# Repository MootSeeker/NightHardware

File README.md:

# NightHardware
PCB for Nightlight project

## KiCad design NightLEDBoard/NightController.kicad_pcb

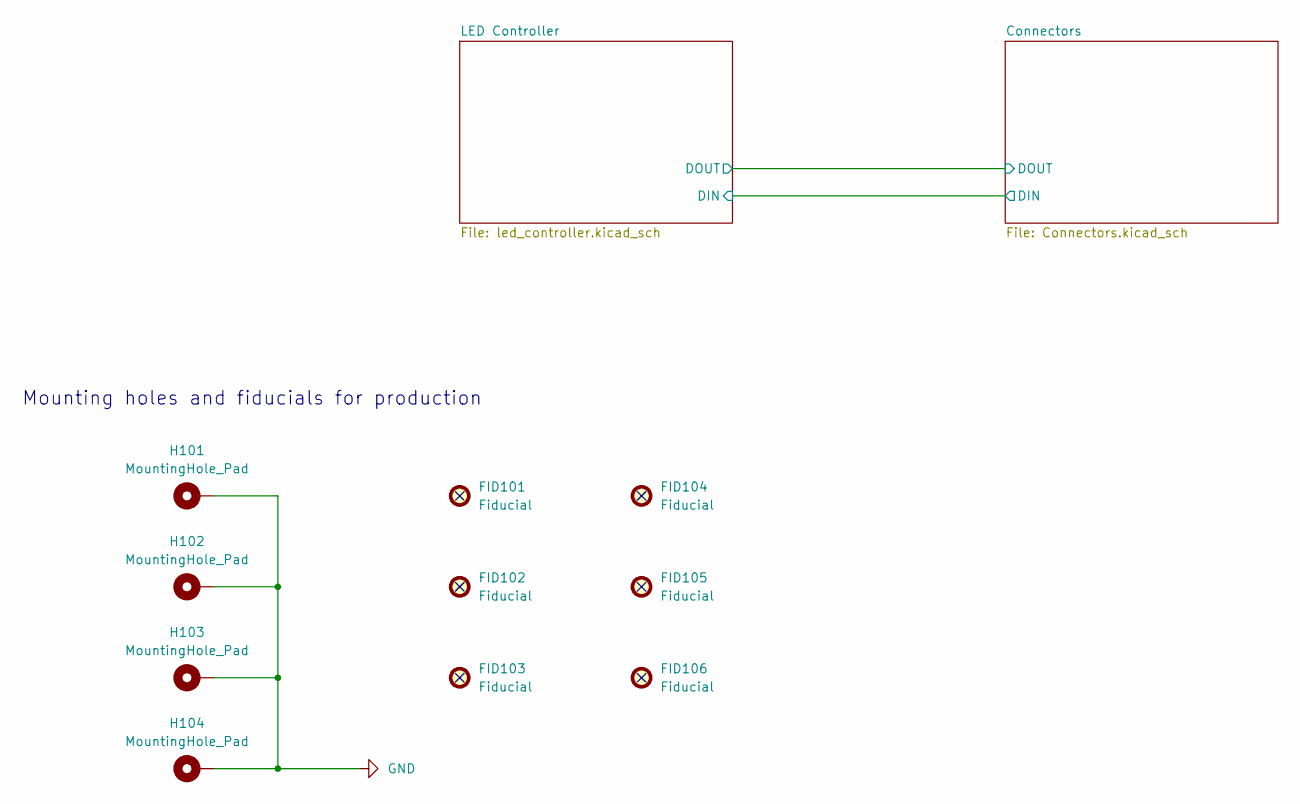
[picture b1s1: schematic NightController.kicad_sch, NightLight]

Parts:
FID101, FID102, FID103, FID104, FID105, FID106: Fiducial; Fiducial_0.5mm_Mask1mm
H101, H102, H103, H104: MountingHole_Pad; MountingHole_3.2mm_M3_Pad_Via

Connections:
GND: H101.1, H102.1, H103.1, H104.1; also elsewhere on the board

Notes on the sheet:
Mounting holes and fiducials for production

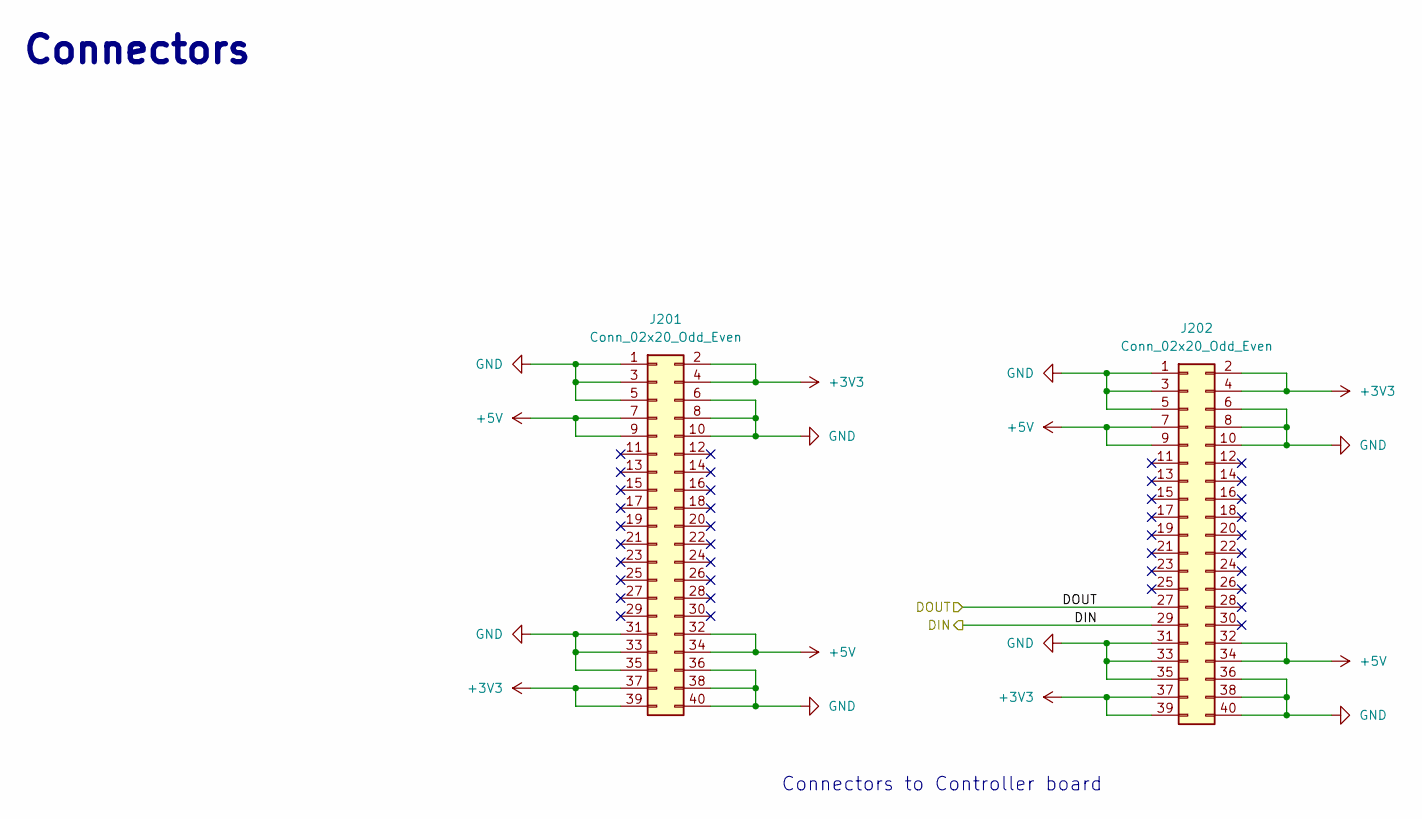
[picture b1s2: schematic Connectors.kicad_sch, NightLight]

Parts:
J201, J202: Conn_02x20_Odd_Even; Molex_SlimStack_54722-0404_2x20_P0.50mm_Vertical

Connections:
+3V3: J201.2, J201.4, J201.37, J201.39, J202.2, J202.4, J202.37, J202.39
+5V: J201.7, J201.9, J201.32, J201.34, J202.7, J202.9, J202.32, J202.34; also elsewhere on the board
/Connectors/DIN: J202.29; also elsewhere on the board
/Connectors/DOUT: J202.27; also elsewhere on the board
GND: J201.1, J201.3, J201.5, J201.6, J201.8, J201.10, J201.31, J201.33, J201.35, J201.36, J201.38, J201.40, J202.1, J202.3, J202.5, J202.6, J202.8, J202.10, J202.31, J202.33, J202.35, J202.36, J202.38, J202.40; also elsewhere on the board

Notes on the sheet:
Connectors to Controller board
Connectors

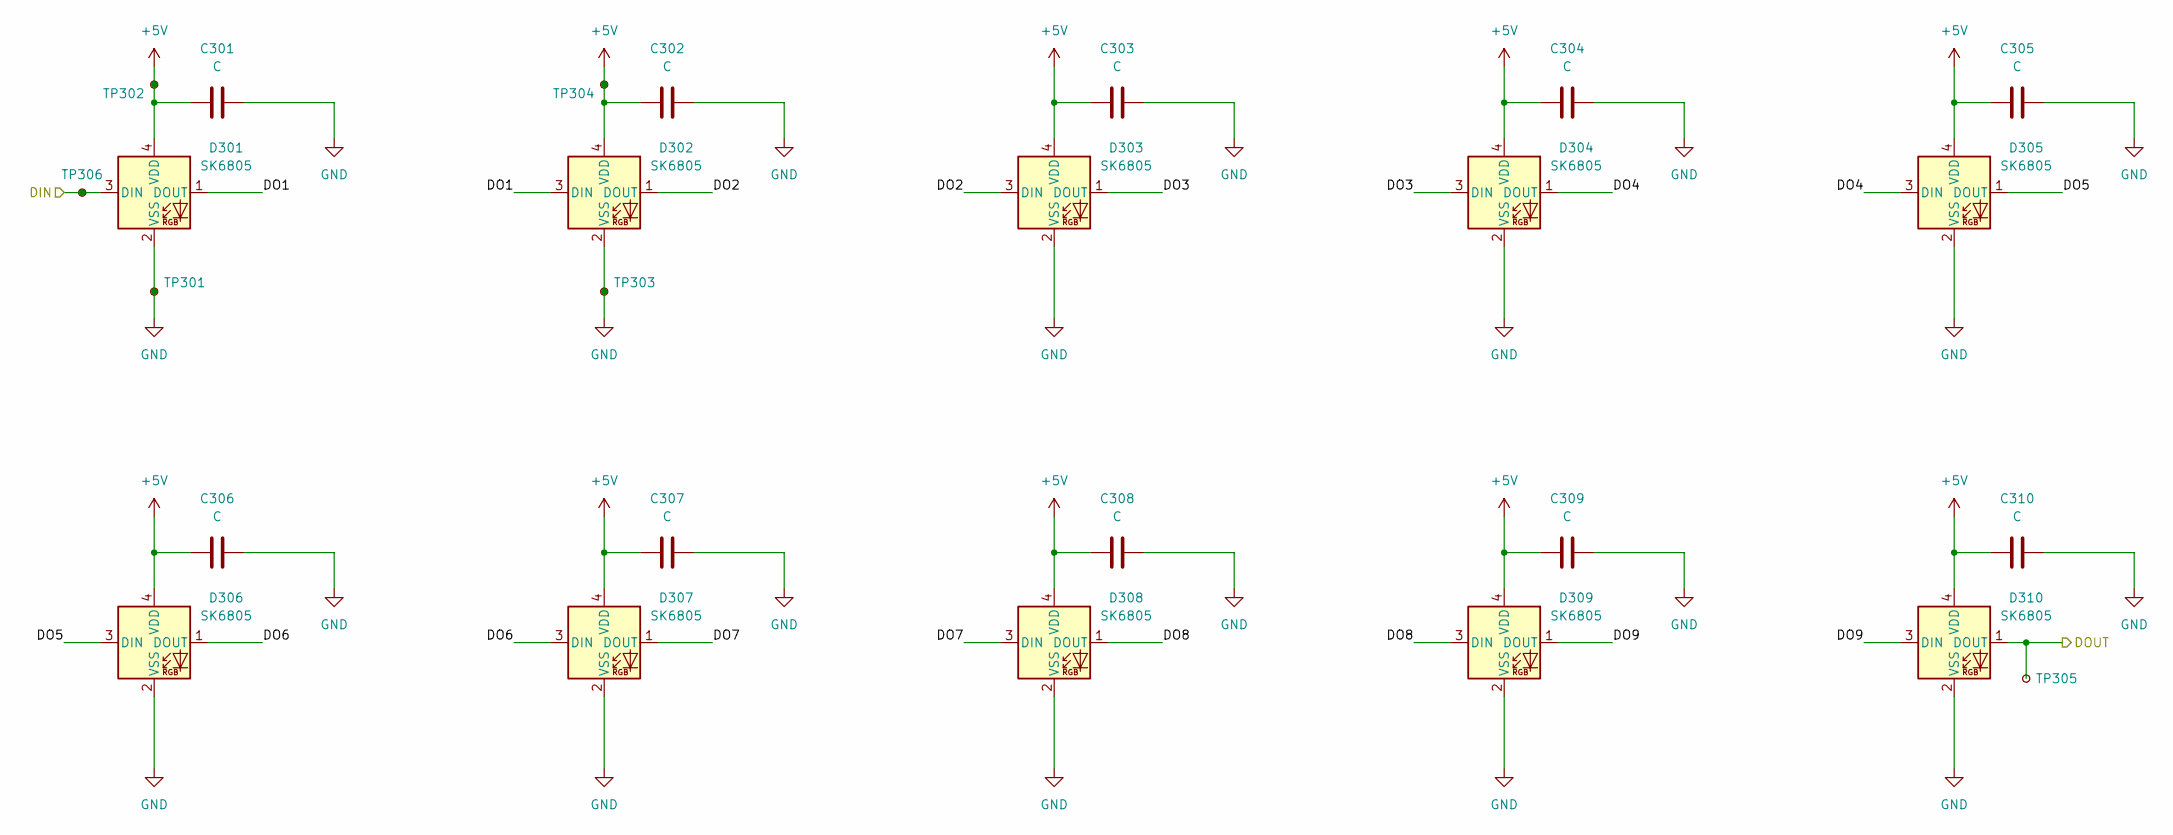
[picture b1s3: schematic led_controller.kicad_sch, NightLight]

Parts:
C301, C302, C303, C304, C305, C306, C307, C308, C309, C310: C; C_0402_1005Metric_Pad0.74x0.62mm_HandSolder
D301, D302, D303, D304, D305, D306, D307, D308, D309, D310: SK6805; LED_SK6805_PLCC4_2.4x2.7mm_P1.3mm
TP301, TP302, TP303, TP304, TP305, TP306: TestPoint_Small; TestPoint_Loop_D1.80mm_Drill1.0mm_Beaded

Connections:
+5V: C301.1, C302.1, C303.1, C304.1, C305.1, C306.1, C307.1, C308.1, C309.1, C310.1, D301.4 (VDD), D302.4 (VDD), D303.4 (VDD), D304.4 (VDD), D305.4 (VDD), D306.4 (VDD), D307.4 (VDD), D308.4 (VDD), D309.4 (VDD), D310.4 (VDD), TP302.1, TP304.1; also elsewhere on the board
/Connectors/DIN: D301.3 (DIN), TP306.1; also elsewhere on the board
/Connectors/DOUT: D310.1 (DOUT), TP305.1; also elsewhere on the board
/LED Controller/DO1: D301.1 (DOUT), D302.3 (DIN)
/LED Controller/DO2: D302.1 (DOUT), D303.3 (DIN)
/LED Controller/DO3: D303.1 (DOUT), D304.3 (DIN)
/LED Controller/DO4: D304.1 (DOUT), D305.3 (DIN)
/LED Controller/DO5: D305.1 (DOUT), D306.3 (DIN)
/LED Controller/DO6: D306.1 (DOUT), D307.3 (DIN)
/LED Controller/DO7: D307.1 (DOUT), D308.3 (DIN)
/LED Controller/DO8: D308.1 (DOUT), D309.3 (DIN)
/LED Controller/DO9: D309.1 (DOUT), D310.3 (DIN)
GND: C301.2, C302.2, C303.2, C304.2, C305.2, C306.2, C307.2, C308.2, C309.2, C310.2, D301.2 (VSS), D302.2 (VSS), D303.2 (VSS), D304.2 (VSS), D305.2 (VSS), D306.2 (VSS), D307.2 (VSS), D308.2 (VSS), D309.2 (VSS), D310.2 (VSS), TP301.1, TP303.1; also elsewhere on the board

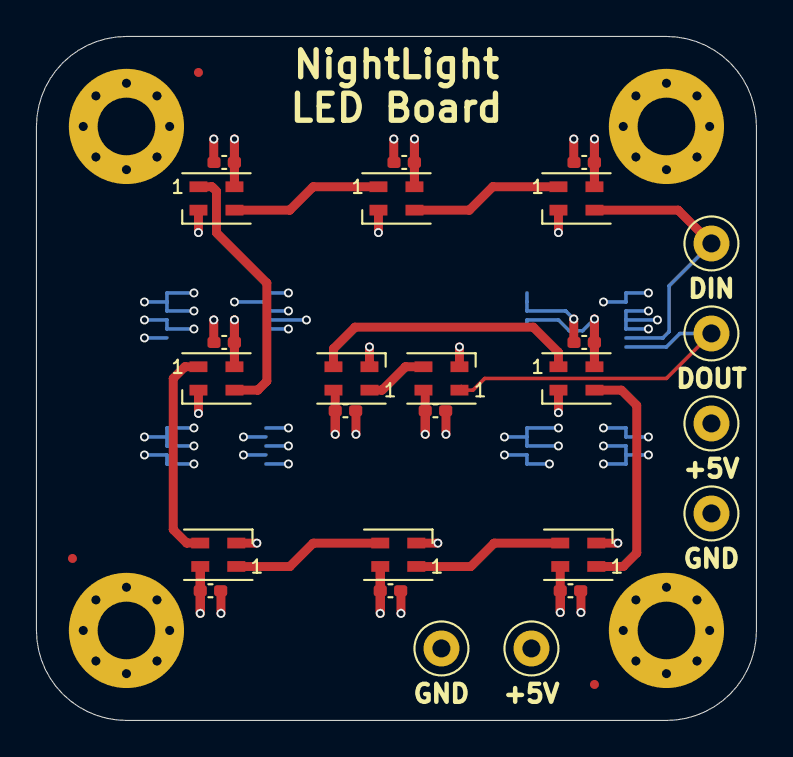
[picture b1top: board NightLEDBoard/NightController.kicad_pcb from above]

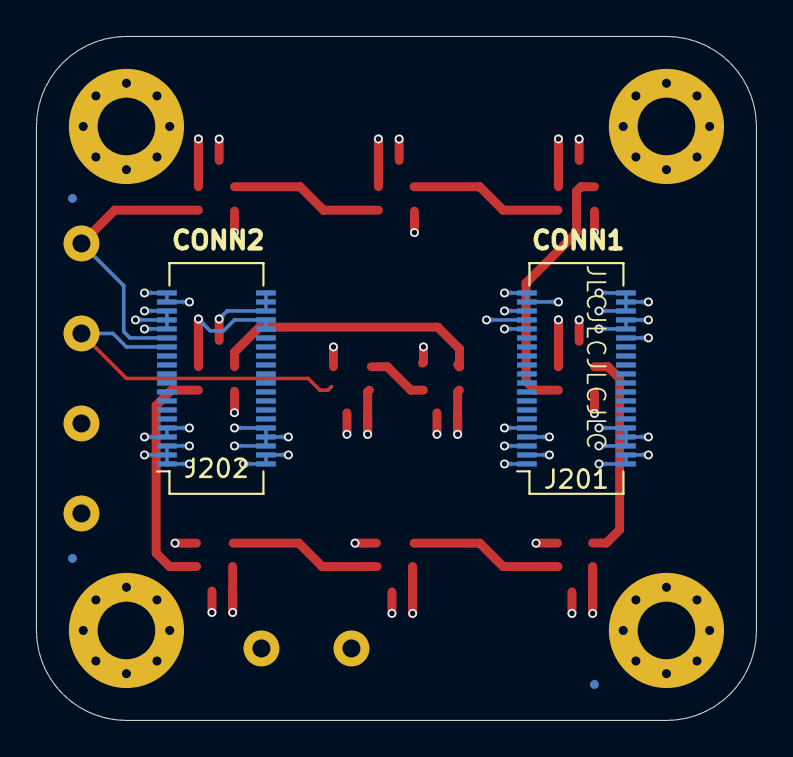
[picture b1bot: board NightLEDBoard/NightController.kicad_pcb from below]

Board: 4 copper layers, 40.0 x 38.0 mm, 38 parts (5 on the bottom side), 14 nets.

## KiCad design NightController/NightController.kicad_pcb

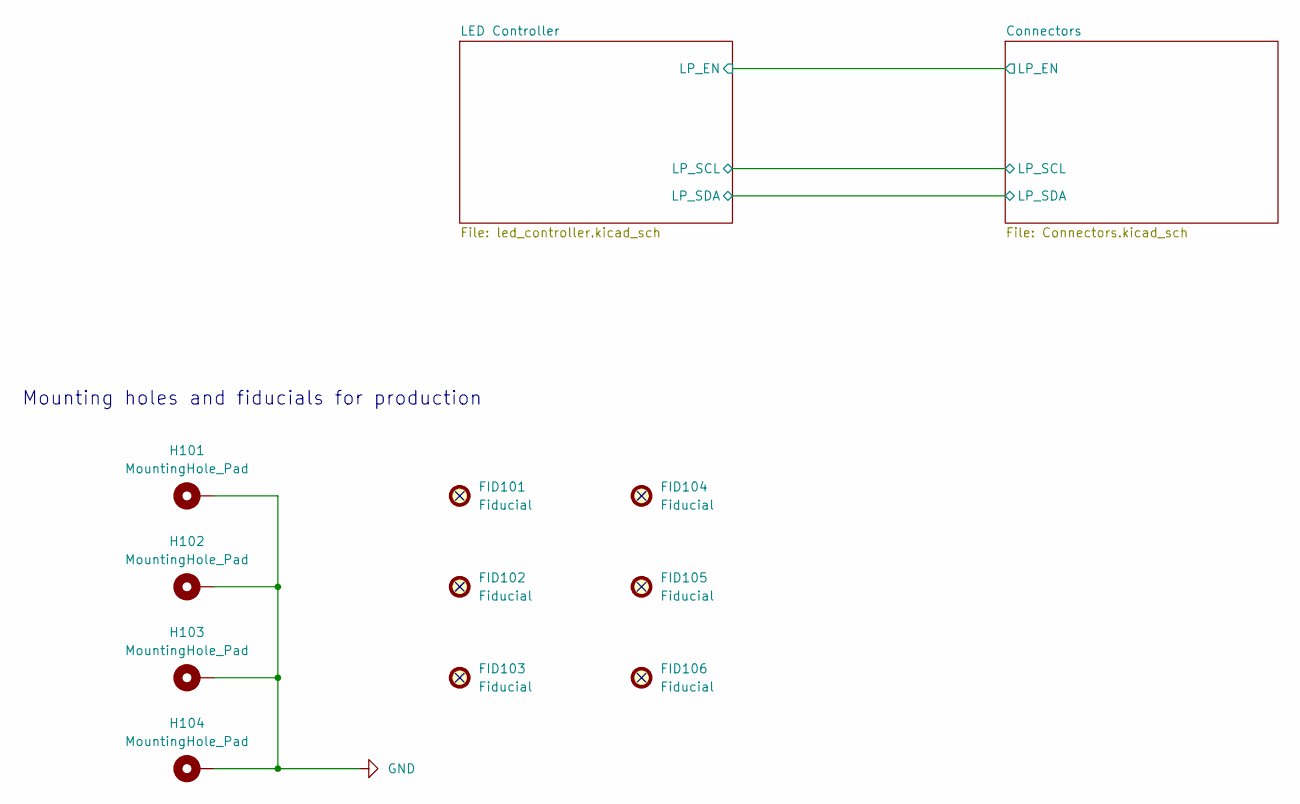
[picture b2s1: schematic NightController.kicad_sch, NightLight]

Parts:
FID101, FID102, FID103, FID104, FID105, FID106: Fiducial; Fiducial_0.5mm_Mask1mm
H101, H102, H103, H104: MountingHole_Pad; MountingHole_3.2mm_M3_Pad_Via

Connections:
GND: H101.1, H102.1, H103.1, H104.1; also elsewhere on the board

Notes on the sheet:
Mounting holes and fiducials for production

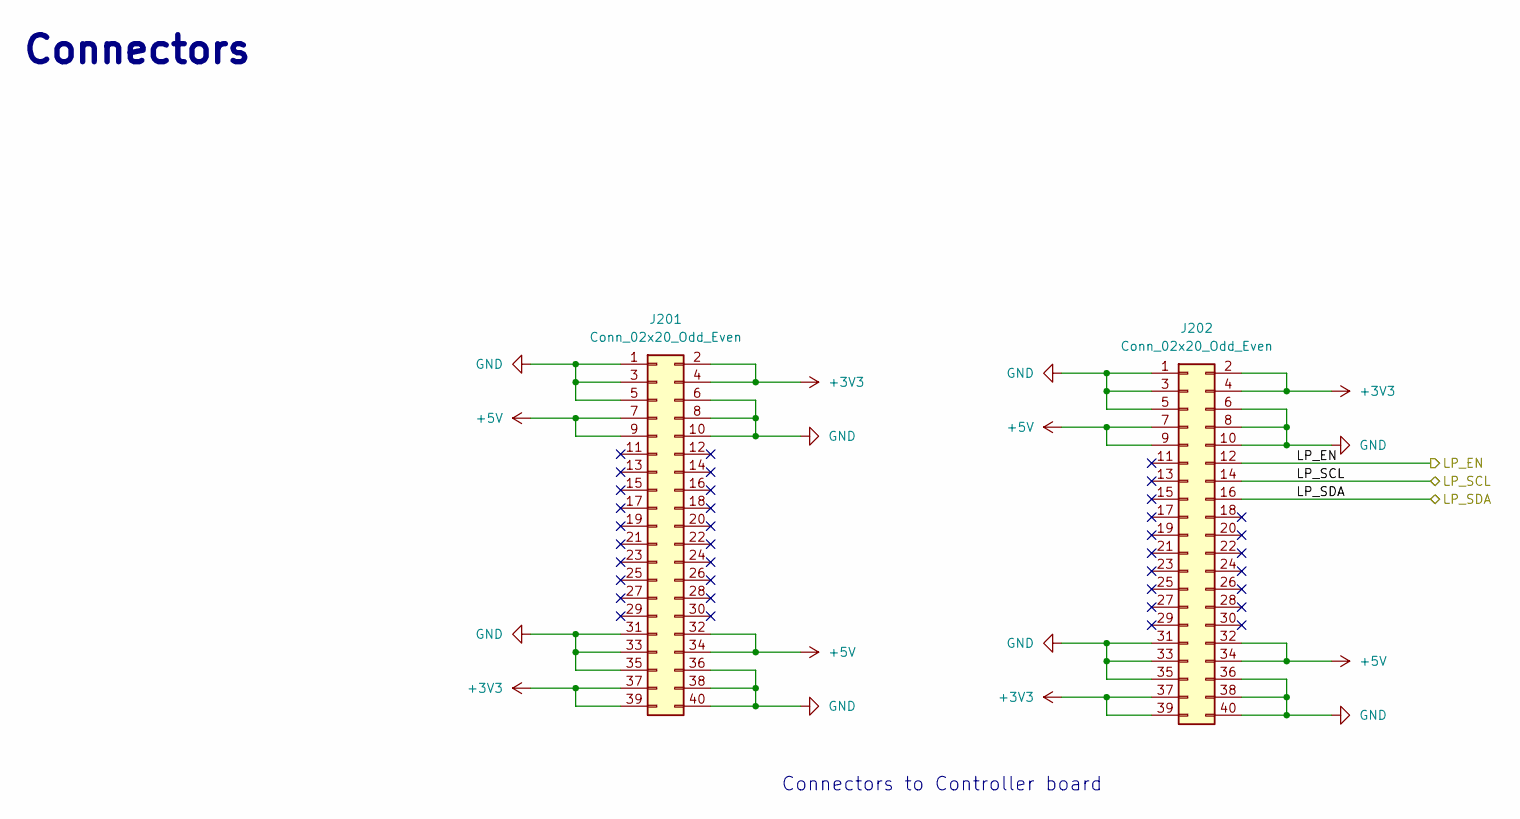
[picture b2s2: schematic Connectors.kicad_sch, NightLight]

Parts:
J201, J202: Conn_02x20_Odd_Even; Molex_SlimStack_54722-0404_2x20_P0.50mm_Vertical

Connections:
+3V3: J201.2, J201.4, J201.37, J201.39, J202.2, J202.4, J202.37, J202.39
+5V: J201.7, J201.9, J201.32, J201.34, J202.7, J202.9, J202.32, J202.34; also elsewhere on the board
/Connectors/LP_EN: J202.12; also elsewhere on the board
/Connectors/LP_SCL: J202.14; also elsewhere on the board
/Connectors/LP_SDA: J202.16; also elsewhere on the board
GND: J201.1, J201.3, J201.5, J201.6, J201.8, J201.10, J201.31, J201.33, J201.35, J201.36, J201.38, J201.40, J202.1, J202.3, J202.5, J202.6, J202.8, J202.10, J202.31, J202.33, J202.35, J202.36, J202.38, J202.40; also elsewhere on the board

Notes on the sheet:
Connectors to Controller board
Connectors

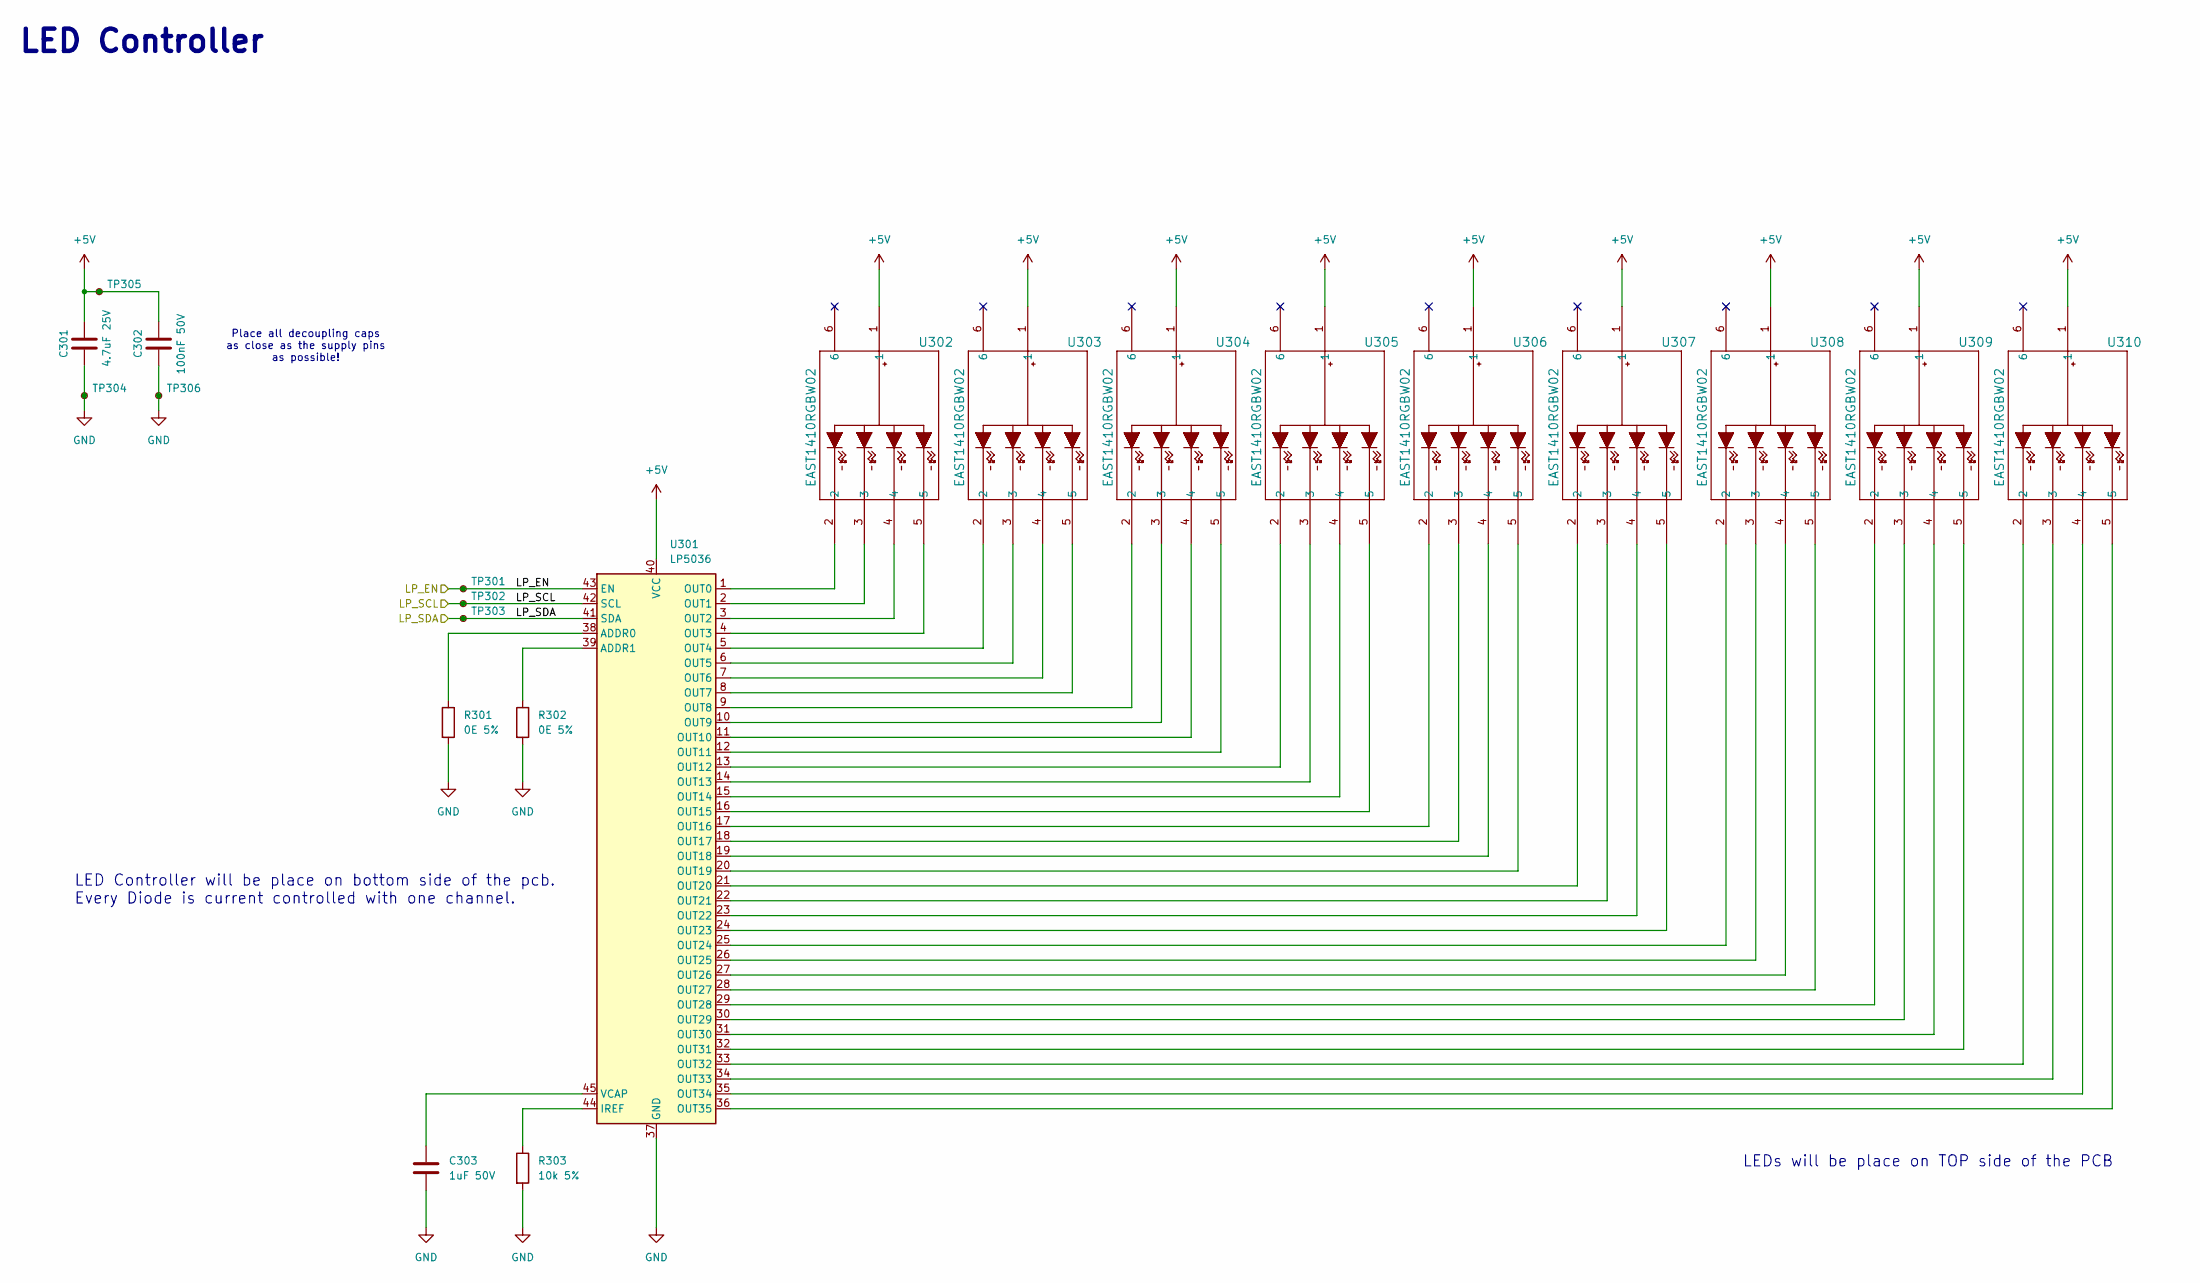
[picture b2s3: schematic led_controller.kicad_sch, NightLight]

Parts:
C301: 4.7uF 25V; C_0402_1005Metric_Pad0.74x0.62mm_HandSolder
C302: 100nF 50V; C_0402_1005Metric_Pad0.74x0.62mm_HandSolder
C303: 1uF 50V; C_0402_1005Metric_Pad0.74x0.62mm_HandSolder
R301, R302: 0E 5%; R_0402_1005Metric_Pad0.72x0.64mm_HandSolder
R303: 10k 5%; R_0402_1005Metric_Pad0.72x0.64mm_HandSolder
TP301, TP302, TP303, TP304, TP305, TP306: TestPoint_Small; TestPoint_Loop_D1.80mm_Drill1.0mm_Beaded
U301: LP5036; VQFN-46-1EP_5x6mm_P0.4mm_EP2.8x3.8mm
U302, U303, U304, U305, U306, U307, U308, U309, U310: EAST1410RGBW02; SMD_EAST1410RGBW02_EVE

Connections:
+5V: C301.1, C302.1, TP305.1, U301.40 (VCC), U302.1, U303.1, U304.1, U305.1, U306.1, U307.1, U308.1, U309.1, U310.1; also elsewhere on the board
/Connectors/LP_EN: TP301.1, U301.43 (EN); also elsewhere on the board
/Connectors/LP_SCL: TP302.1, U301.42 (SCL); also elsewhere on the board
/Connectors/LP_SDA: TP303.1, U301.41 (SDA); also elsewhere on the board
GND: C301.2, C302.2, C303.2, R301.2, R302.2, R303.2, TP304.1, TP306.1, U301.37 (GND), U301.46 (GND), U301.47 (GND); also elsewhere on the board
unnamed: R301.1, U301.38 (ADDR0)
unnamed: R302.1, U301.39 (ADDR1)
unnamed: R303.1, U301.44 (IREF)
unnamed: U301.1 (OUT0), U302.2
unnamed: U301.2 (OUT1), U302.3
unnamed: U301.3 (OUT2), U302.4
unnamed: U301.4 (OUT3), U302.5
unnamed: U301.5 (OUT4), U303.2
unnamed: U301.6 (OUT5), U303.3
unnamed: U301.7 (OUT6), U303.4
unnamed: U301.8 (OUT7), U303.5
unnamed: U301.9 (OUT8), U304.2
unnamed: U301.10 (OUT9), U304.3
unnamed: U301.11 (OUT10), U304.4
unnamed: U301.12 (OUT11), U304.5
unnamed: U301.13 (OUT12), U305.2
unnamed: U301.14 (OUT13), U305.3
unnamed: U301.15 (OUT14), U305.4
unnamed: U301.16 (OUT15), U305.5
unnamed: U301.17 (OUT16), U306.2
unnamed: U301.18 (OUT17), U306.3
unnamed: U301.19 (OUT18), U306.4
unnamed: U301.20 (OUT19), U306.5
unnamed: U301.21 (OUT20), U307.2
unnamed: U301.22 (OUT21), U307.3
unnamed: U301.23 (OUT22), U307.4
unnamed: U301.24 (OUT23), U307.5
unnamed: U301.25 (OUT24), U308.2
unnamed: U301.26 (OUT25), U308.3
unnamed: U301.27 (OUT26), U308.4
unnamed: U301.28 (OUT27), U308.5
unnamed: U301.29 (OUT28), U309.2
unnamed: U301.30 (OUT29), U309.3
unnamed: U301.31 (OUT30), U309.4
unnamed: U301.32 (OUT31), U309.5
unnamed: U301.33 (OUT32), U310.2
unnamed: U301.34 (OUT33), U310.3
unnamed: U301.35 (OUT34), U310.4
unnamed: U301.36 (OUT35), U310.5
unnamed: C303.1, U301.45 (VCAP)

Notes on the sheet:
LEDs will be place on TOP side of the PCB
LED Controller
Place all decoupling caps as close as the supply pins as possible!
LED Controller will be place on bottom side of the pcb. Every Diode is current controlled with one channel.

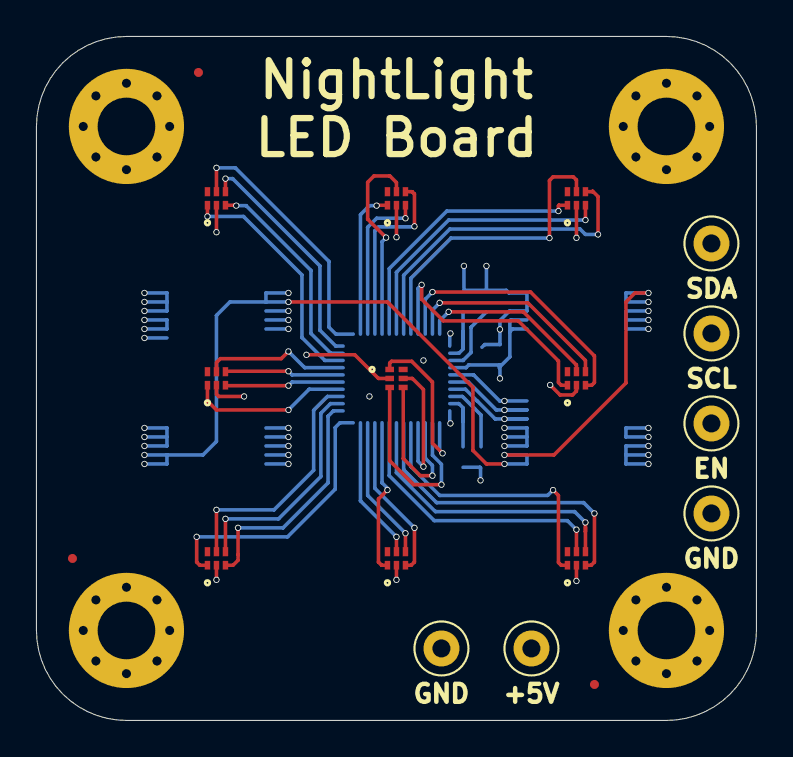
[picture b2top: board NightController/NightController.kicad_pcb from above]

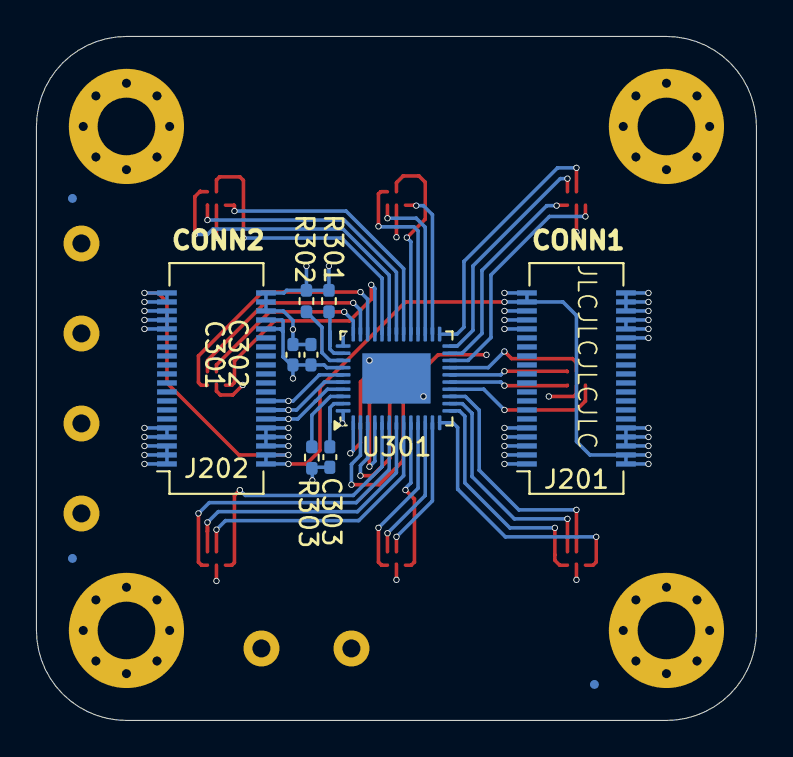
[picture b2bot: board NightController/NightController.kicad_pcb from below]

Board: 4 copper layers, 40.0 x 38.0 mm, 34 parts (12 on the bottom side), 46 nets.

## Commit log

2024-07-10 Add Files
2024-07-11 Add LED lib
2024-07-11 Working on files
2024-07-11 working on LED PCB
2024-07-12 Finisched digital one
2024-07-12 Add second pcb
2024-07-12 Add parts
2024-07-12 Add new symbol
2024-07-14 Working on schematic
2024-07-15 update schematic
2024-07-15 Finished mcu
2024-07-16 Add Right Connector

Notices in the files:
NightController/Connectors.kicad_sch:
MootSeeker (c) 2024
